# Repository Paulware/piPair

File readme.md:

<h1>Raspberry Pi Pairing project</h1>
This project is based on the 10 in Maker Shack laptop (available on ebay): <br>
But, the python code itself can be tested solely on a LAN network with windows pcs (if desired).<p>
The idea is to connect 2 (or more) raspberry pi using the pi's wifi chip and then chat or play games.
<br>Recommended bluetooth keyboard (Logitech K380):<br>

<h2>Classes</h2>
The code is separated into classes<br>
<Table border="2px solid">
<tr><th>Class</th><th>Description</th></tr>
<tr><td>SpriteSheet.py</td><td>Read a spritesheet containing all card images</td></tr>
<tr><td>Deck.py</td><td>Create a deck from the spritesheet</td></tr>
<tr><td>SubDeck.py</td><td>"Deal" a sub deck from the deck and display it</td></tr>
<tr><td>PlayingCards.py</td><td>Utility class for standard 52 card playing deck</td></tr>
<tr><td>UnoCards.py</td><td>Utility class for Uno playing deck</td><tr>
<tr><td>Solitaire.py</td><td>The classic solo game</td></tr>
<tr><td>Uno.py</td><td>The game</td></tr>
</table>
<hr>
<p>

Code is written in python in a module fashion so that students can add more games.<br>
Currently the games that are supported are:
<ul>
  <li>Chat (not really a game but the basis of all game communication)</li>
  <li>Tic Tac Toe</li>
  <li>Checkers</li>
  <li>Chess</li>
  <li>Tank (battle)</li>
  <li>MTG (Magic the Gathering)</li>
  <li>Uno</li>
  <li>Diplomacy (in progress)</li>
</ul>
<h1>Raspberry Pi Setup</h1>
<ul>
  <li>Download the latest raspbian image from: <a href="https://www.raspberrypi.org/downloads/raspbian">https://www.raspberrypi.org/downloads/raspbian</a></li>
  <li>Copy the .img to an 8gb sd card using <a href="https://www.sourceforge.net/projects/win32diskimager">win32diskimager</a></li>
  <li>Copy the setup.sh file to the sd card (this will be later referred to as /boot area)</li>
  <li>Connect an internet cable to the raspberry pi</li>
  <li>Place the sd card in the raspberry pi and power up</li>
  <li>Open a line terminal and enter the commands</li>
  <ul>
     <li>sudo bash</li>
     <li>cd /boot</li>
     <li>pip install pygame_widgets</li>
     <li>./setup.sh</li>
     <li>Let the setup.sh complete (this will take a few minutes)</li>
     <li>Turn on wifi (via desktop icon)</li>
     <li>Pair to your bluetooth keyboard (via bluetooth icon)</li>
     <li>reboot - The game should appear and an access point with SSID=Walker and password=ABCD1234</li>
  </ul>
</ul>

<h3>Keyboard Logitech K380 Setup</h3>
<ul>
   <li>Press and hold yellow key 1 until it blinks</li>
   <li>Using the bluetooth icon on the raspberry pi</li>
     <ul>
       <li>Turn on bluetooth</li>
       <li>Make Discoverable</li>
       <li>Select K380 Keyboard in list of devices</li>
     </ul>
     <li>Enter the number in the K380 keyboard as directed by the raspberry pi</li>
</ul>
<H1>Design</H1>
   <a href="http://paulware.github.io/piPair">Doc</a>

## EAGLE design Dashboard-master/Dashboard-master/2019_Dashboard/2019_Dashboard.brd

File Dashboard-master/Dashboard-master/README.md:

View this project on [CADLAB.io](https://cadlab.io/project/1315). 

# Dashboard

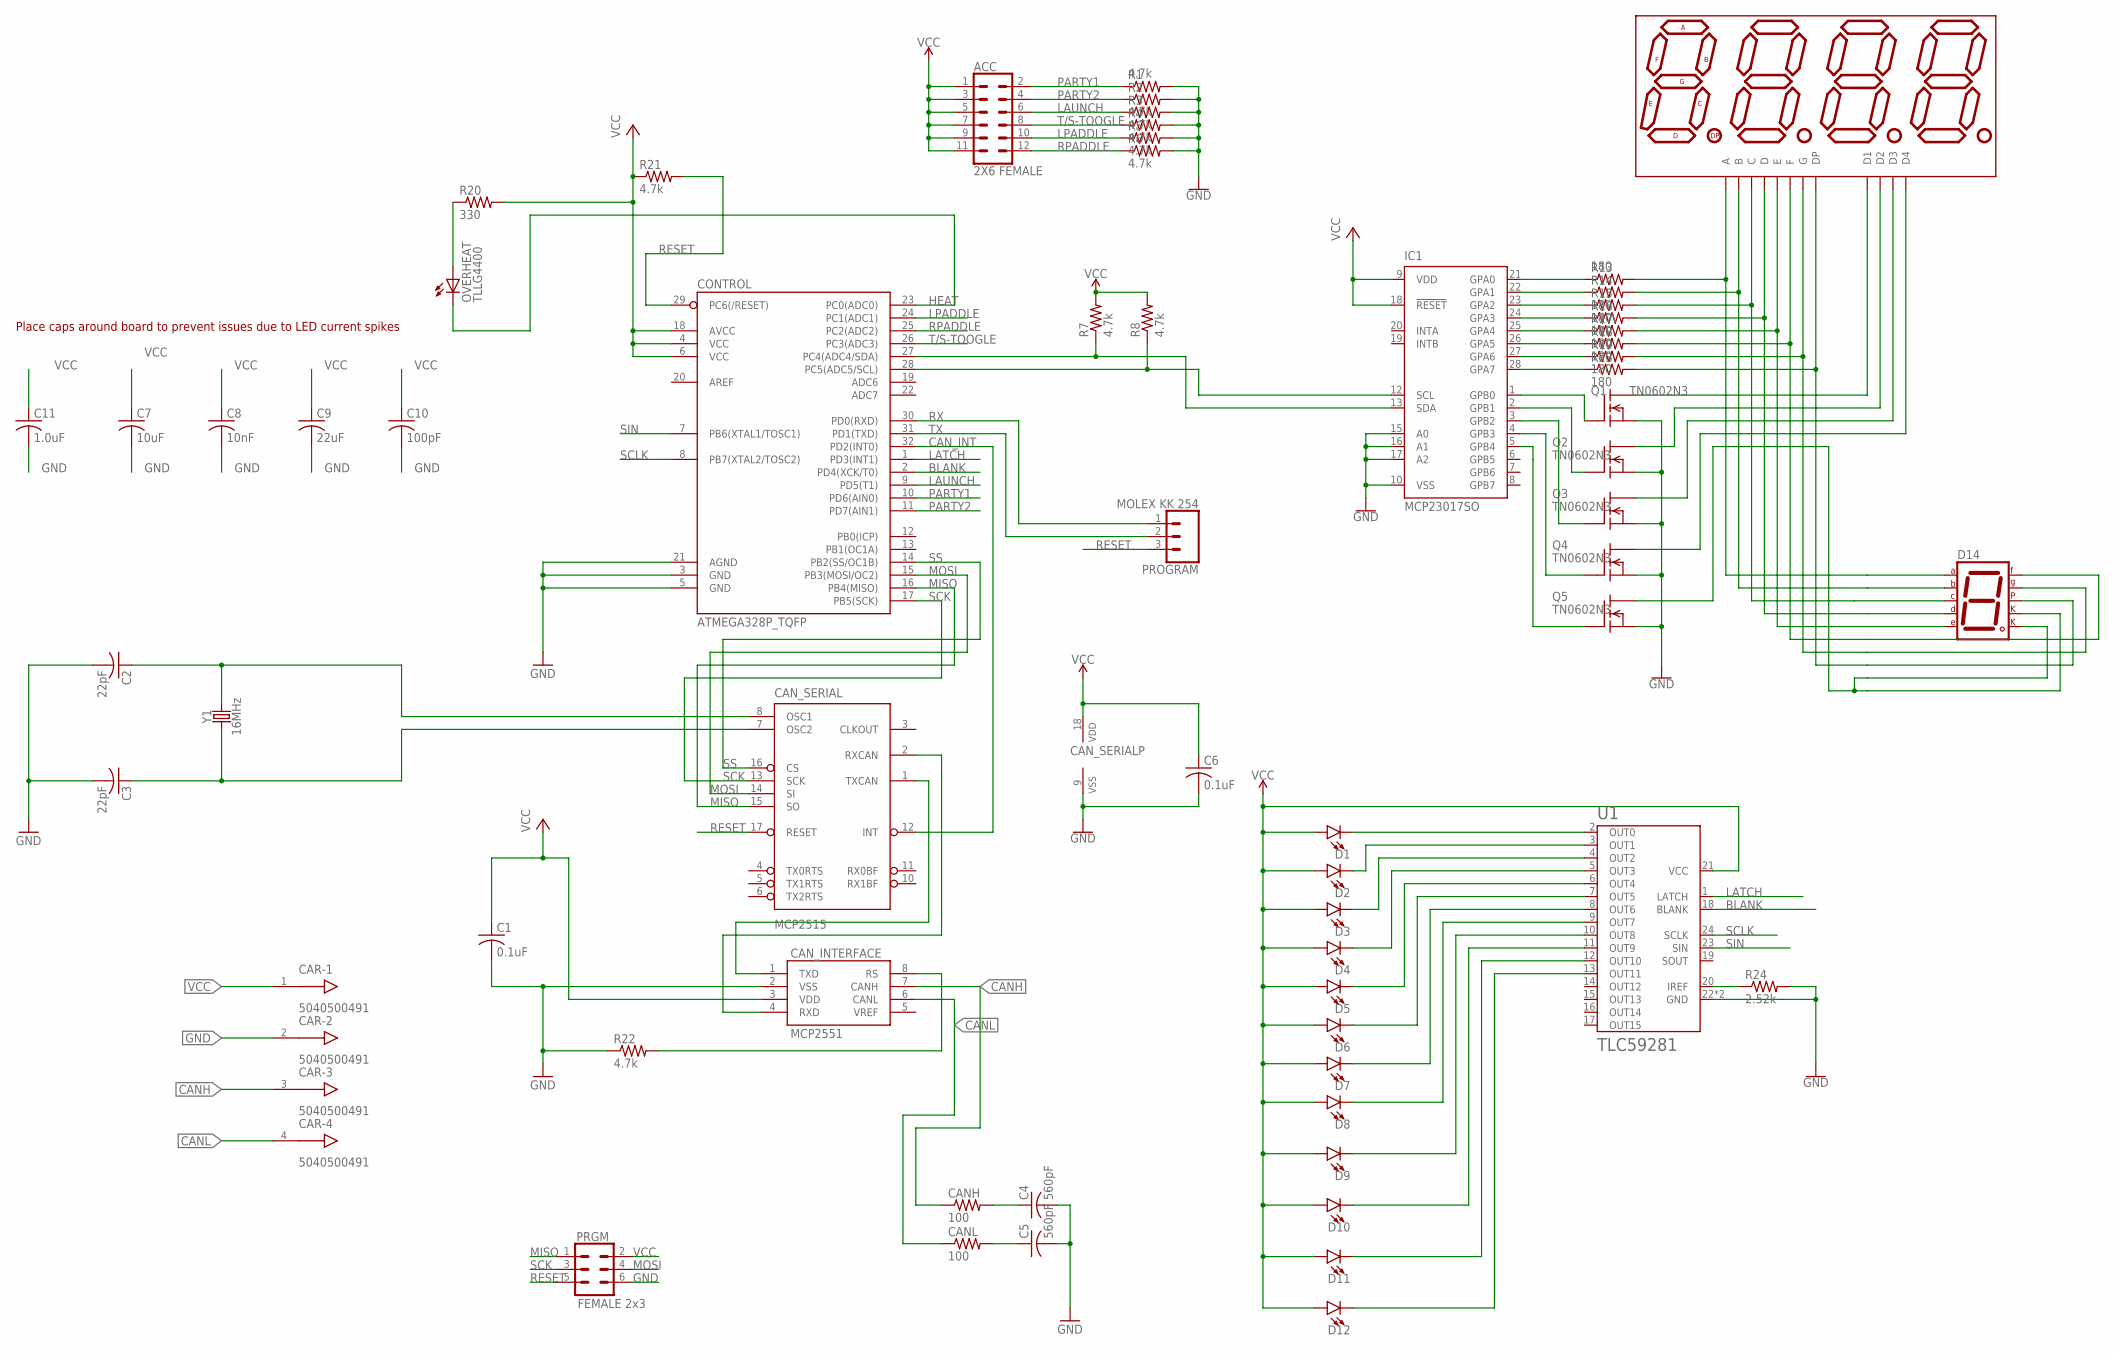
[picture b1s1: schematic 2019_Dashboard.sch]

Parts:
ACC: 2X6 FEMALE; 2X6
C1, C6: 0.1uF; C0603
C2, C3: 22pF; C0603
C4, C5: 560pF; C0603
C7: 10uF; C0603
C8: 10nF; C0603
C9: 22uF; C0603
C10: 100pF; C0603
C11: 1.0uF; C0603
CANH: 100; R0603
CANL: 100; R0603
CAN_INTERFACE: MCP2551; SO08
CAN_SERIAL: MCP2515; SO18W
CAR: 5040500491; PICOLOCK505050-0491
CONTROL: ATMEGA328P_TQFP; TQFP32-08
D1, D2, D3, D4, D5, D6, D7, D8, D9, D10, D11, D12: LED5MM; LED_5MM
D14: 7SEG-CK; 7SEG-13
DISP1: ATA8041ARBJ; 7-SEGMENT-4DIGIT-20MM
IC1: MCP23017SO; SO28W
OVERHEAT: TLLG4400; LED3MM
PRGM: FEMALE 2x3; 2X3
PROGRAM: MOLEX KK 254; 1X03
Q1, Q2, Q3, Q4, Q5: TN0602N3; TO-92
R1, R2, R3, R4, R5, R6, R7, R8, R21, R22: 4.7k; R0603
R13, R14, R16, R17, R18, R19, R23: 180; R0603
R15: 180\; R0603
R20: 330; R0603
R24: 2.52k; R0603
U1: TLC59281; QFN-24
Y1: 16MHz; HC49US

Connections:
BLANK: CONTROL.2 (PD4(XCK/T0)), U1.18 (BLANK)
CANH: CANH.1, CAN_INTERFACE.7 (CANH), CAR.3
CANL: CANL.1, CAN_INTERFACE.6 (CANL), CAR.4
CAN_INT: CAN_SERIAL.12 (INT), CONTROL.32 (PD2(INT0))
CHI: C4.1, CANH.2
CI_SLOPE: CAN_INTERFACE.8 (RS), R22.2
CLI: C5.1, CANL.2
GND: C1.2, C2.2, C3.2, C4.2, C5.2, C6.2, C7.2, C8.2, C9.2, C10.2, C11.2, CAN_INTERFACE.2 (VSS), CAN_SERIAL.9 (VSS), CAR.2, CONTROL.3 (GND), CONTROL.5 (GND), CONTROL.21 (AGND), IC1.10 (VSS), IC1.15 (A0), IC1.16 (A1), IC1.17 (A2), PRGM.6, Q1.1 (S), Q2.1 (S), Q3.1 (S), Q4.1 (S), Q5.1 (S), R1.2, R2.2, R3.2, R4.2, R5.2, R6.2, R22.1, R24.2, U1.22 (GND), U1.EP (GND)
HEAT: CONTROL.23 (PC0(ADC0)), OVERHEAT.K (C)
HEAT+: OVERHEAT.A, R20.1
LATCH: CONTROL.1 (PD3(INT1)), U1.1 (LATCH)
LAUNCH: ACC.6, CONTROL.9 (PD5(T1)), R3.1
LPADDLE: ACC.10, CONTROL.24 (PC1(ADC1)), R5.1
MISO: CAN_SERIAL.15 (SO), CONTROL.16 (PB4(MISO)), PRGM.1
MOSI: CAN_SERIAL.14 (SI), CONTROL.15 (PB3(MOSI/OC2)), PRGM.4
unnamed: CONTROL.28 (PC5(ADC5/SCL)), IC1.12 (SCL), R8.1
unnamed: CONTROL.27 (PC4(ADC4/SDA)), IC1.13 (SDA), R7.1
unnamed: D14.7 (A), DISP1.11 (A), R13.2
unnamed: D14.6 (B), DISP1.7 (B), R14.2
unnamed: D14.4 (C), DISP1.4 (C), R15.2
unnamed: D14.2 (D), DISP1.2 (D), R16.2
unnamed: D14.1 (E), DISP1.1 (E), R17.2
unnamed: D14.9 (F), DISP1.10 (F), R18.2
unnamed: D14.10 (G), DISP1.5 (G), R19.2
unnamed: D14.5 (DP), DISP1.3 (DP), R23.2
unnamed: DISP1.12 (D1), Q1.3 (D)
unnamed: DISP1.9 (D2), Q2.3 (D)
unnamed: DISP1.8 (D3), Q3.3 (D)
unnamed: DISP1.6 (D4), Q4.3 (D)
unnamed: D14.3 (CK1), D14.8 (CK2), Q5.3 (D)
unnamed: IC1.21 (GPA0), R13.1
unnamed: IC1.22 (GPA1), R14.1
unnamed: IC1.23 (GPA2), R15.1
unnamed: IC1.24 (GPA3), R16.1
unnamed: IC1.25 (GPA4), R17.1
unnamed: IC1.26 (GPA5), R18.1
unnamed: IC1.27 (GPA6), R19.1
unnamed: IC1.28 (GPA7), R23.1
unnamed: IC1.1 (GPB0), Q1.2 (G)
unnamed: IC1.2 (GPB1), Q2.2 (G)
unnamed: IC1.3 (GPB2), Q3.2 (G)
unnamed: IC1.4 (GPB3), Q4.2 (G)
unnamed: IC1.5 (GPB4), Q5.2 (G)
unnamed: D1.K (C), U1.2 (OUT0)
unnamed: D2.K (C), U1.3 (OUT1)
unnamed: D3.K (C), U1.4 (OUT2)
unnamed: D4.K (C), U1.5 (OUT3)
unnamed: CAN_INTERFACE.1 (TXD), CAN_SERIAL.1 (TXCAN)
unnamed: CAN_INTERFACE.4 (RXD), CAN_SERIAL.2 (RXCAN)
unnamed: D5.K (C), U1.6 (OUT4)
unnamed: D6.K (C), U1.7 (OUT5)
unnamed: D7.K (C), U1.8 (OUT6)
unnamed: D8.K (C), U1.9 (OUT7)
unnamed: D9.K (C), U1.10 (OUT8)
unnamed: D10.K (C), U1.11 (OUT9)
unnamed: D11.K (C), U1.12 (OUT10)
unnamed: D12.K (C), U1.13 (OUT11)
unnamed: R24.1, U1.20 (IREF)
OSC1: C2.1, CAN_SERIAL.8 (OSC1), Y1.2
OSC2: C3.1, CAN_SERIAL.7 (OSC2), Y1.1
PARTY1: ACC.2, CONTROL.10 (PD6(AIN0)), R1.1
PARTY2: ACC.4, CONTROL.11 (PD7(AIN1)), R2.1
RESET: CAN_SERIAL.17 (RESET), CONTROL.29 (PC6(/RESET)), PRGM.5, PROGRAM.3, R21.2
RPADDLE: ACC.12, CONTROL.25 (PC2(ADC2)), R6.1
RX: CONTROL.30 (PD0(RXD)), PROGRAM.1
SCK: CAN_SERIAL.13 (SCK), CONTROL.17 (PB5(SCK)), PRGM.3
SCLK: CONTROL.8 (PB7(XTAL2/TOSC2)), U1.24 (SCLK)
SIN: CONTROL.7 (PB6(XTAL1/TOSC1)), U1.23 (SIN)
SS: CAN_SERIAL.16 (CS), CONTROL.14 (PB2(SS/OC1B))
T/S-TOOGLE: ACC.8, CONTROL.26 (PC3(ADC3)), R4.1
TX: CONTROL.31 (PD1(TXD)), PROGRAM.2
VCC: ACC.1, ACC.3, ACC.5, ACC.7, ACC.9, ACC.11, C1.1, C6.1, C7.1, C8.1, C9.1, C10.1, C11.1, CAN_INTERFACE.3 (VDD), CAN_SERIAL.18 (VDD), CAR.1, CONTROL.4 (VCC), CONTROL.6 (VCC), CONTROL.18 (AVCC), D1.A, D2.A, D3.A, D4.A, D5.A, D6.A, D7.A, D8.A, D9.A, D10.A, D11.A, D12.A, IC1.9 (VDD), IC1.18 (!RESET), PRGM.2, R7.2, R8.2, R20.2, R21.1, U1.21 (VCC)

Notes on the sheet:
Place caps around board to prevent issues due to LED current spikes

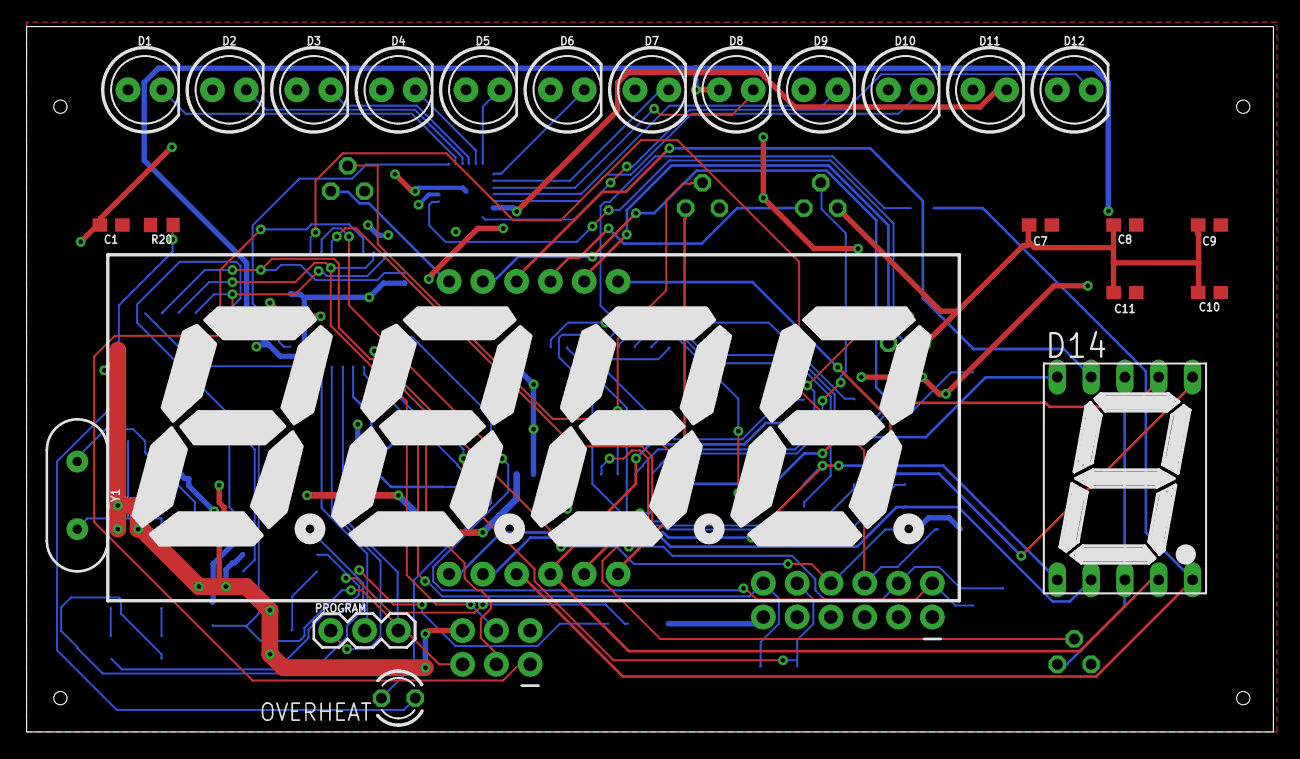
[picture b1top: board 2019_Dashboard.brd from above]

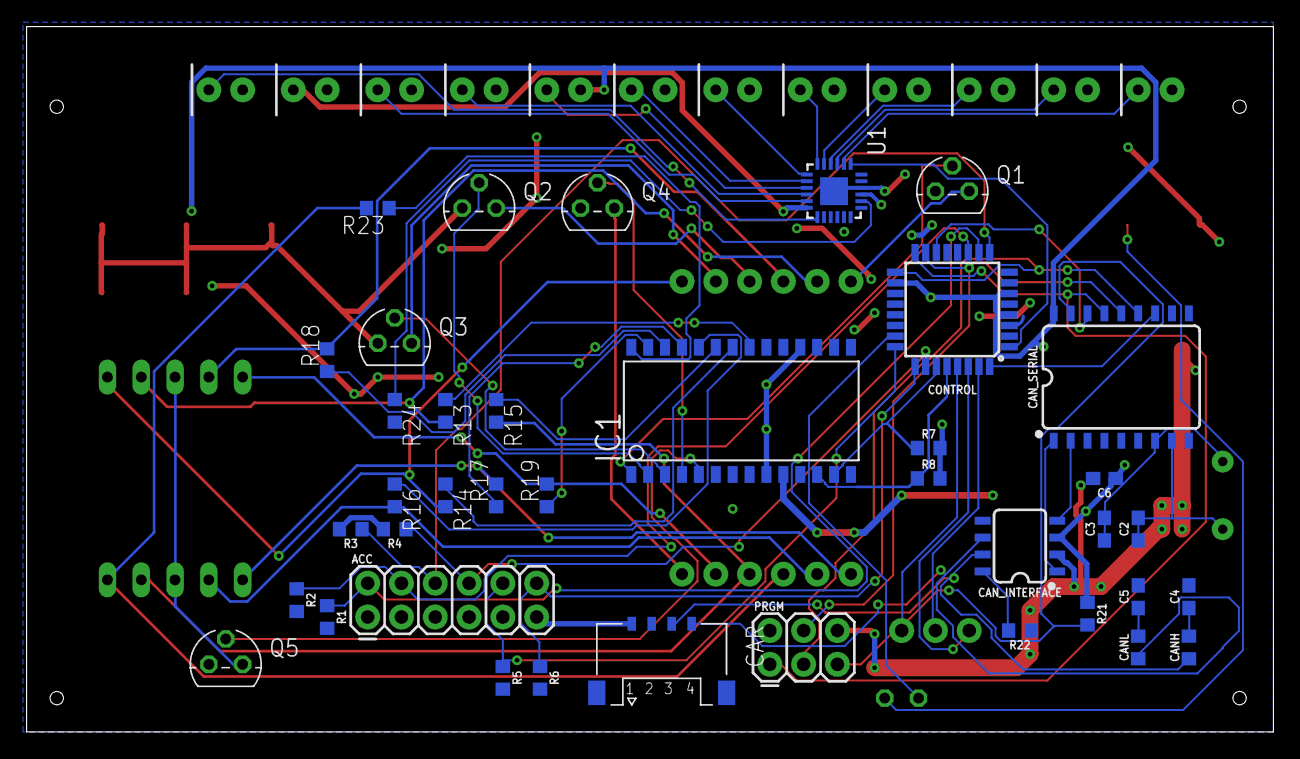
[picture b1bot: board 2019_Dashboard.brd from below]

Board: 2 copper layers, 93.7 x 53.0 mm, 63 parts (39 on the bottom side), 72 nets.

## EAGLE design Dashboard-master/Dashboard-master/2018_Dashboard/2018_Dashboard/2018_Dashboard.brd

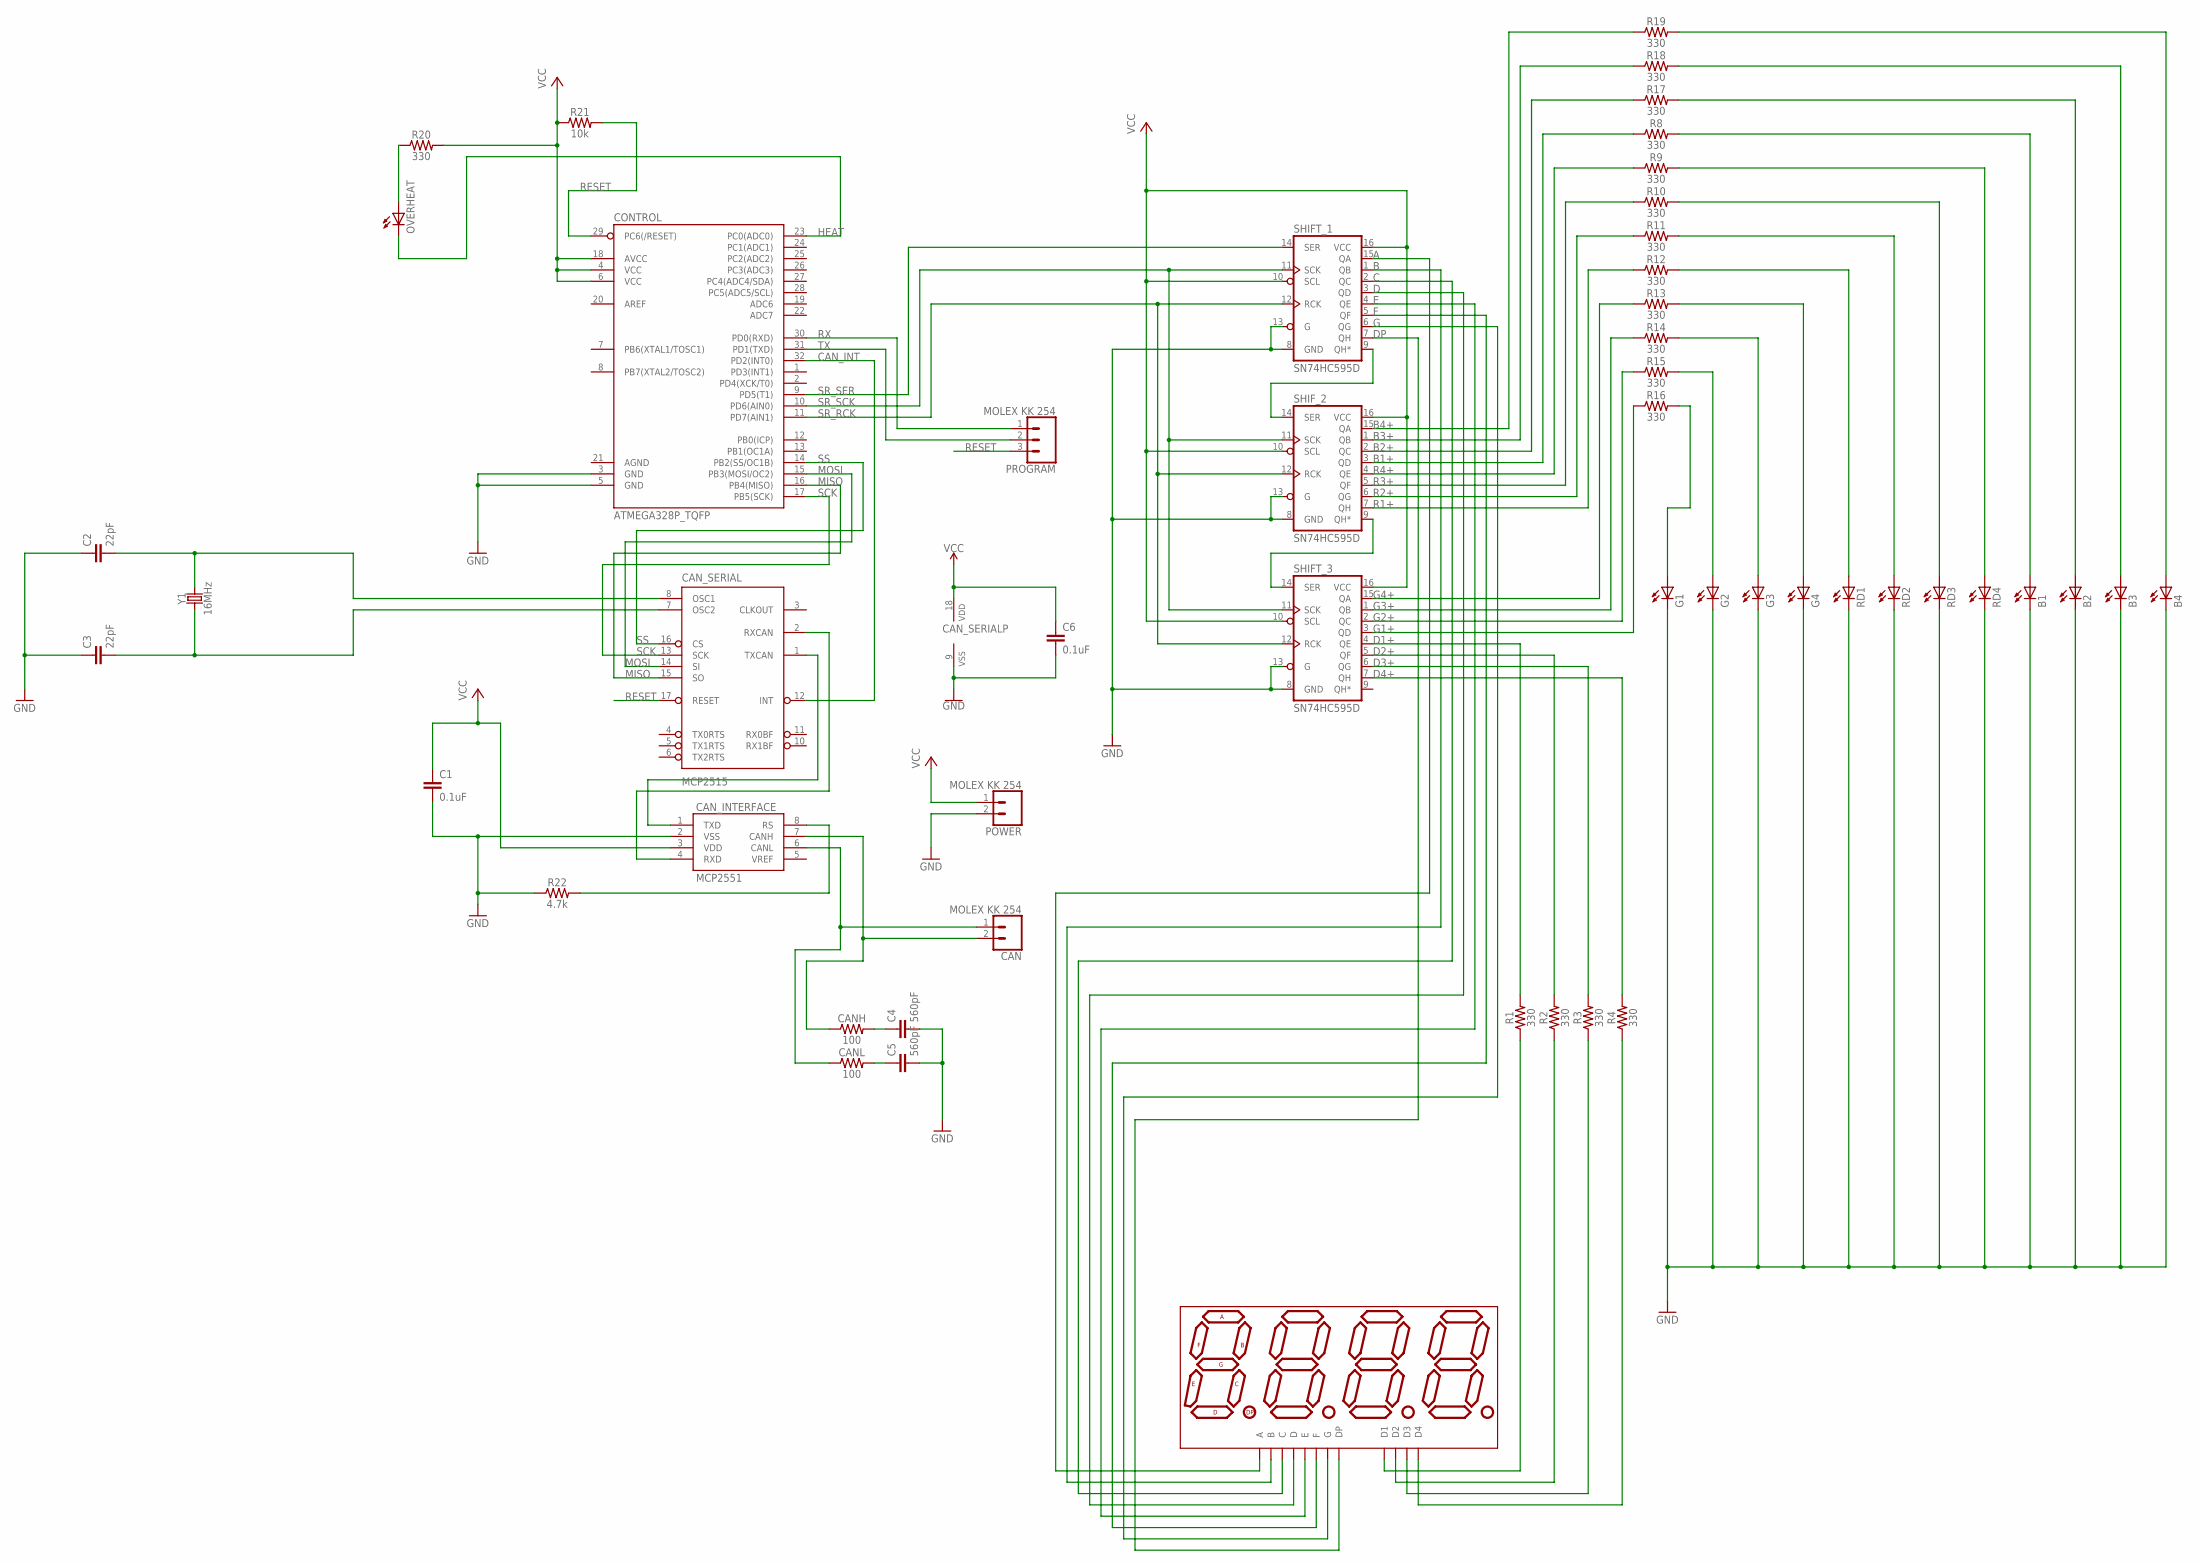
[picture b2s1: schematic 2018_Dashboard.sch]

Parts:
B1, B2, B3, B4: TLLG4400; LED3MM
C1: 0.1uF; 0603
C2, C3: 22pF; 0603
C4, C5: 560pF; 0603
C6: 0.1uF; 0402
CAN: MOLEX KK 254; 1X02
CANH: 100; 0603
CANL: 100; 0603
CAN_INTERFACE: MCP2551; SO08
CAN_SERIAL: MCP2515; SO18W
CONTROL: ATMEGA328P_TQFP; TQFP32-08
G1, G2, G3, G4: TLLG4400; LED3MM
OVERHEAT: TLLG4400; LED3MM
POWER: MOLEX KK 254; 1X02
PROGRAM: MOLEX KK 254; 1X03
R1, R2, R3, R4, R8, R9, R10, R11, R12, R13, R14, R15, R16, R17, R18, R19, R20: 330; 0603
R21: 10k; 0603
R22: 4.7k; 0603
RD1, RD2, RD3, RD4: TLLG4400; LED3MM
SEVEN_SEGMENT: ATA8041AB; 7-SEGMENT-4DIGIT-20MM
SHIFT_1, SHIFT_3: SN74HC595D; SO16
SHIF_2: SN74HC595D; SO16
Y1: 16MHz; HC49US

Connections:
A: SEVEN_SEGMENT.11 (A), SHIFT_1.15 (QA)
B: SEVEN_SEGMENT.7 (B), SHIFT_1.1 (QB)
B1: B1.A, R8.2
B1+: R8.1, SHIF_2.3 (QD)
B2: B2.A, R17.2
B2+: R17.1, SHIF_2.2 (QC)
B3: B3.A, R18.2
B3+: R18.1, SHIF_2.1 (QB)
B4: B4.A, R19.2
B4+: R19.1, SHIF_2.15 (QA)
C: SEVEN_SEGMENT.4 (C), SHIFT_1.2 (QC)
CANH: CAN.2, CANH.1, CAN_INTERFACE.7 (CANH)
CANL: CAN.1, CANL.1, CAN_INTERFACE.6 (CANL)
CAN_INT: CAN_SERIAL.12 (INT), CONTROL.32 (PD2(INT0))
CARRY1: SHIFT_1.9 (QH*), SHIF_2.14 (SER)
CARRY2: SHIFT_3.14 (SER), SHIF_2.9 (QH*)
CHI: C4.1, CANH.2
CI_SLOPE: CAN_INTERFACE.8 (RS), R22.2
CLI: C5.1, CANL.2
D: SEVEN_SEGMENT.2 (D), SHIFT_1.3 (QD)
D1: R1.1, SEVEN_SEGMENT.12 (D1)
D1+: R1.2, SHIFT_3.4 (QE)
D2: R2.1, SEVEN_SEGMENT.9 (D2)
D2+: R2.2, SHIFT_3.5 (QF)
D3: R3.1, SEVEN_SEGMENT.8 (D3)
D3+: R3.2, SHIFT_3.6 (QG)
D4: R4.1, SEVEN_SEGMENT.6 (D4)
D4+: R4.2, SHIFT_3.7 (QH)
DP: SEVEN_SEGMENT.3 (DP), SHIFT_1.7 (QH)
E: SEVEN_SEGMENT.1 (E), SHIFT_1.4 (QE)
F: SEVEN_SEGMENT.10 (F), SHIFT_1.5 (QF)
G: SEVEN_SEGMENT.5 (G), SHIFT_1.6 (QG)
G1: G1.A, R16.2
G1+: R16.1, SHIFT_3.3 (QD)
G2: G2.A, R15.2
G2+: R15.1, SHIFT_3.2 (QC)
G3: G3.A, R14.2
G3+: R14.1, SHIFT_3.1 (QB)
G4: G4.A, R13.2
G4+: R13.1, SHIFT_3.15 (QA)
GND: B1.K (C), B2.K (C), B3.K (C), B4.K (C), C1.2, C2.1, C3.1, C4.2, C5.2, C6.2, CAN_INTERFACE.2 (VSS), CAN_SERIAL.9 (VSS), CONTROL.3 (GND), CONTROL.5 (GND), G1.K (C), G2.K (C), G3.K (C), G4.K (C), POWER.2, R22.1, RD1.K (C), RD2.K (C), RD3.K (C), RD4.K (C), SHIFT_1.8 (GND), SHIFT_1.13 (G), SHIFT_3.8 (GND), SHIFT_3.13 (G), SHIF_2.8 (GND), SHIF_2.13 (G)
HEAT: CONTROL.23 (PC0(ADC0)), OVERHEAT.K (C)
HEAT+: OVERHEAT.A, R20.1
MISO: CAN_SERIAL.15 (SO), CONTROL.16 (PB4(MISO))
MOSI: CAN_SERIAL.14 (SI), CONTROL.15 (PB3(MOSI/OC2))
unnamed: CAN_INTERFACE.1 (TXD), CAN_SERIAL.1 (TXCAN)
unnamed: CAN_INTERFACE.4 (RXD), CAN_SERIAL.2 (RXCAN)
OSC1: C2.2, CAN_SERIAL.8 (OSC1), Y1.2
OSC2: C3.2, CAN_SERIAL.7 (OSC2), Y1.1
R1: R12.2, RD1.A
R1+: R12.1, SHIF_2.7 (QH)
R2: R11.2, RD2.A
R2+: R11.1, SHIF_2.6 (QG)
R3: R10.2, RD3.A
R3+: R10.1, SHIF_2.5 (QF)
R4: R9.2, RD4.A
R4+: R9.1, SHIF_2.4 (QE)
RESET: CAN_SERIAL.17 (RESET), CONTROL.29 (PC6(/RESET)), PROGRAM.3, R21.2
RX: CONTROL.30 (PD0(RXD)), PROGRAM.1
SCK: CAN_SERIAL.13 (SCK), CONTROL.17 (PB5(SCK))
SR_RCK: CONTROL.11 (PD7(AIN1)), SHIFT_1.12 (RCK), SHIFT_3.12 (RCK), SHIF_2.12 (RCK)
SR_SCK: CONTROL.10 (PD6(AIN0)), SHIFT_1.11 (SCK), SHIFT_3.11 (SCK), SHIF_2.11 (SCK)
SR_SER: CONTROL.9 (PD5(T1)), SHIFT_1.14 (SER)
SS: CAN_SERIAL.16 (CS), CONTROL.14 (PB2(SS/OC1B))
TX: CONTROL.31 (PD1(TXD)), PROGRAM.2
VCC: C1.1, C6.1, CAN_INTERFACE.3 (VDD), CAN_SERIAL.18 (VDD), CONTROL.4 (VCC), CONTROL.6 (VCC), CONTROL.18 (AVCC), POWER.1, R20.2, R21.1, SHIFT_1.10 (SCL), SHIFT_1.16 (VCC), SHIFT_3.10 (SCL), SHIFT_3.16 (VCC), SHIF_2.10 (SCL), SHIF_2.16 (VCC)

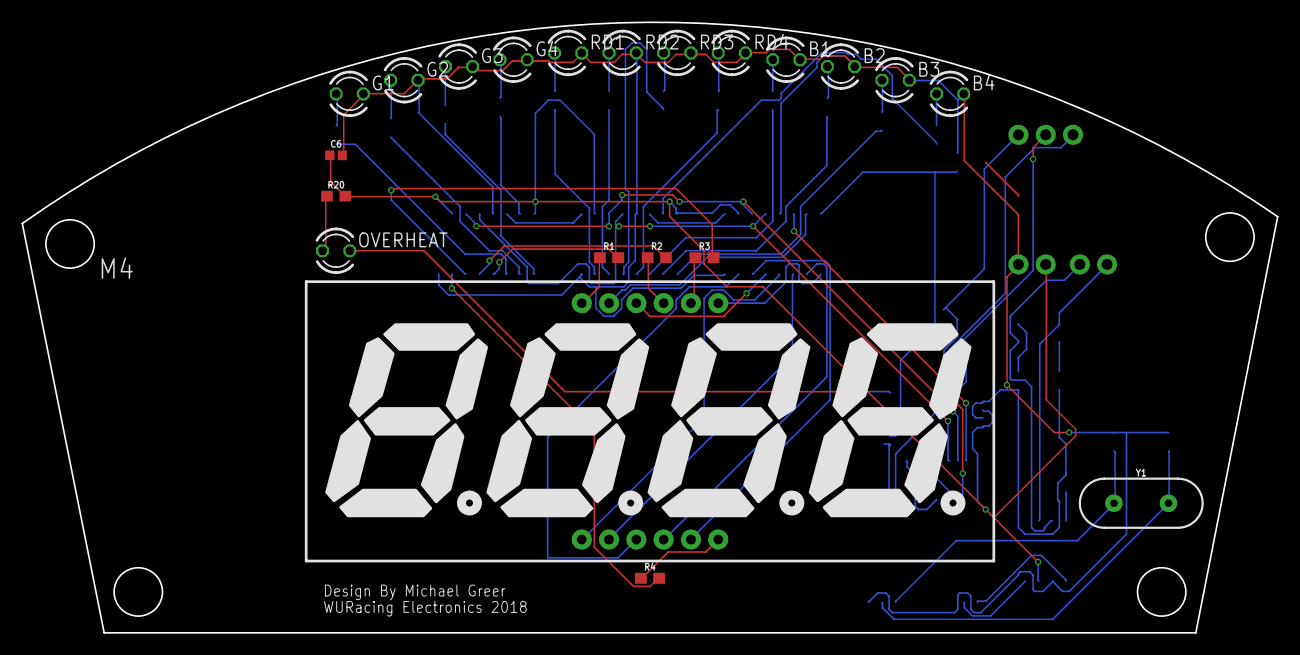
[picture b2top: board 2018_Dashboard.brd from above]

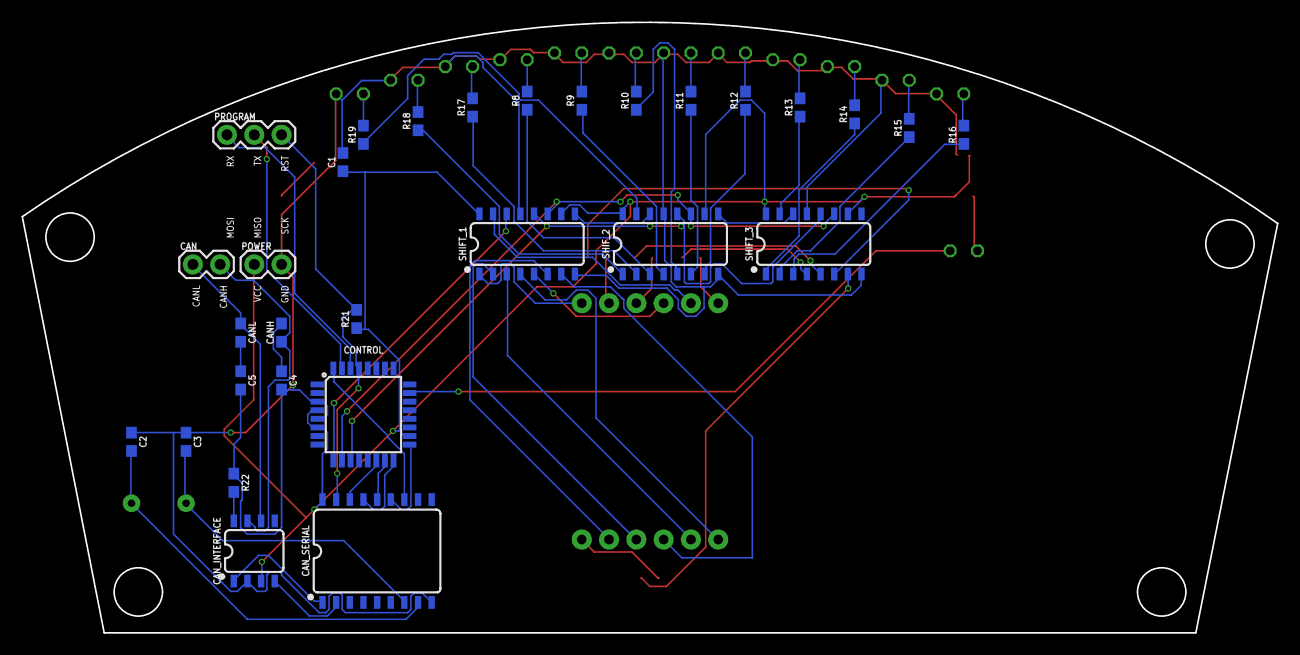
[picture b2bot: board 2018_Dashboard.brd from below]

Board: 2 copper layers, 116.8 x 56.8 mm, 51 parts (30 on the bottom side), 66 nets.

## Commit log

2020-03-29 Modified main.py
2020-03-29 modified drawO
2020-03-29 drawO
2020-03-29 taken
2020-03-30 Checkers
2020-03-30 Tictactoe separate file
2020-03-31 Checkers'
2020-03-31 Chess
2020-03-31 piPair
2020-04-01 Reorganize
2020-04-01 readme
2020-04-02 Tank update
2020-04-02 Tank
2020-04-04 gitignore
2020-04-04 iAmHost
2020-04-04 tankType
2020-04-04 remove prints
2020-04-04 Remove debug prints
2020-04-04 show move
2020-04-04 Explosion
2020-04-04 Lost
2020-04-04 Show games updated
2020-04-04 Tank show games
2020-04-04 Lables
2020-04-04 Chat
2020-04-04 Waiting on hot
2020-04-04 Waiting in checkers
2020-04-04 Ti tac toe
2020-04-04 tic tac toe
2020-04-04 Shot
2020-04-04 files
2020-04-07 Adjusted mana cost
2020-04-07 summoned
2020-04-08 keyboard
2020-04-08 setup
2020-04-08 wait
2020-04-08 jointimeout
2020-04-08 udpbroadcast
2020-04-08 move
2020-04-08 mainConfig.txt
2020-04-08 Changes?
2020-04-08 hostTurn
2020-04-08 turndone
2020-04-08 buttons
2020-04-08 cast
2020-04-08 opponenCards
2020-04-08 myTurn
2020-04-09 Diplomacy
2020-04-10 ifup wlan0
2020-04-11 change
2020-04-13 resync every ten seconds
2020-04-13 images
2020-04-14 Board
2020-04-16 Add docs
2020-04-16 docs
2020-04-16 Add raspberry pi setup file
2020-04-17 raspberry pi setup
2020-04-17 pi setup
2020-04-17 show image
2020-04-17 raspberry
2020-04-17 showImage
2020-04-17 Lists
2020-04-17 Add image example
2020-04-17 Diplomacy design
2020-04-17 update nearest city
2020-04-17 findlocation
2020-04-17 orders
2020-04-18 executeOrders
2020-04-18 drawFlag
2020-04-18 flag
2020-04-18 rules
2020-04-19 diplomacy doc
2020-04-19 Heng long pinout
2020-04-20 UDPTIMEOUT = 0.1
2020-04-21 listen
2020-04-21 add variant images
2020-04-21 pycache
2020-04-21 try remove
2020-04-23 Unix conversion
2020-04-27 utilityScreens
2020-04-27 git.ignore
2020-05-01 Tapped
2020-05-03 inputoutput
2020-05-04 turn done
2020-05-05 comments
2020-05-12 ap.sh
2020-06-06 move buffer
2022-06-01 solitaire
2022-06-08 update'
2022-06-13 added mosquitto
2022-06-13 corrected
2022-08-20 unoCards
2022-08-23 utilities.flip()
2022-08-25 update solitaire
2023-03-08 Update-finished a game uno
2023-03-20 update mtgCards
2023-07-19 Added Globals.py, and globalDictionary
2023-10-07 Ignore .venv folder
2023-10-09 Added testCommands
2023-10-16 update line 263 Uno.py look for '0'
2023-10-16 'replay' to line 263 Uno.py
2024-01-17 Uno tested out successfully, not using SubDeck

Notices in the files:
parts and their libraries:
SparkFun-Capacitors: Licensing: Creative Commons ShareAlike 4.0 International - https://creativecommons.org/licenses/by-sa/4.0
volks73-Molex: Creative Commons Attribution-ShareAlike 3.0 Unported (CC BY-SA 3.0), http://creativecommons.org/licenses/by-sa/3.0/.
